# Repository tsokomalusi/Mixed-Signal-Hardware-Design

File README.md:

# Mixed-Signal-Hardware-Design

## 📌 Project Summary
This repository contains a mixed-signal hardware design project covering system-level design, schematic capture, analog simulation, and PCB layout.  
The project demonstrates best practices in analog/digital partitioning, component selection, simulation-driven design, and manufacturable PCB layout.

------------------------------------------------------------------------------------------------------------------------------------------------------------------------------------------
## 🧰 Tools Used
- **KiCad** – Schematic capture and PCB design  
- **LTSpice** – Analog circuit simulation  
- **STM32CubeIDE** – MCU pinout planning  
- **draw.io** – System block diagram
- **git and github** - version control system
-----------------------------------------------------------------------------------------------------------------------------------------------------------------------------------------
## 🧱 System Block Diagram

Refined version

-----------------------------------------------------------------------------------------------------------------------------------------------------------------------------------------
## 🧩 Pinout Planning

-----------------------------------------------------------------------------------------------------------------------------------------------------------------------------------------
## 📐 Schematic Design

Root Sheet

Power circuitry

MCU circuitry

ADC circuirty

DAC circuitry

Key design considerations:
- Proper decoupling and grounding
- Separation of analog and digital domains
- Power integrity and signal integrity

------------------------------------------------------------------------------------------------------------------------------------------------------------------------------------------
## 🧩 PCB Layout

### PCB STACKUP 
- TOP LAYER :     SIG/POWER
- IN1 LAYER:      GND
- IN2 LAYER:      GND
- BOTTOM LAYER:   SIG/POWER

###  PCB All Layers

### Top Layer

### Bottom Layer

### 3D View

PCB design highlights:
- Footprint creation
- Controlled impedance traces
- Avoiding: crosstalk, coupling, ground loops, inductance and radiation
- Via stitching, power puddles, keeping proper spacing between analog and digital circuits

-------------------------------------------------------------------------------------------------------------------------------------------------------------------------------------------
## 🔬 LTSpice Simulation

### AC Analysis Schematic

### AC Analysis Response

### DC Operating Point Analysis

------------------------------------------------------------------------------------------------------------------------------------------------------------------------------------------
## 📜 License
This project is released for educational and portfolio purposes.

------------------------------------------------------------------------------------------------------------------------------------------------------------------------------------------
## 🙏 Acknowledgements

This project was developed as part of hands-on learning inspired by the course:

**“Mixed-Signal Hardware Design with KiCad”**  
Instructor: **Philip Salmony**  
Platform: **FEDEVEL Academy**  
Website: https://www.fedevel.com

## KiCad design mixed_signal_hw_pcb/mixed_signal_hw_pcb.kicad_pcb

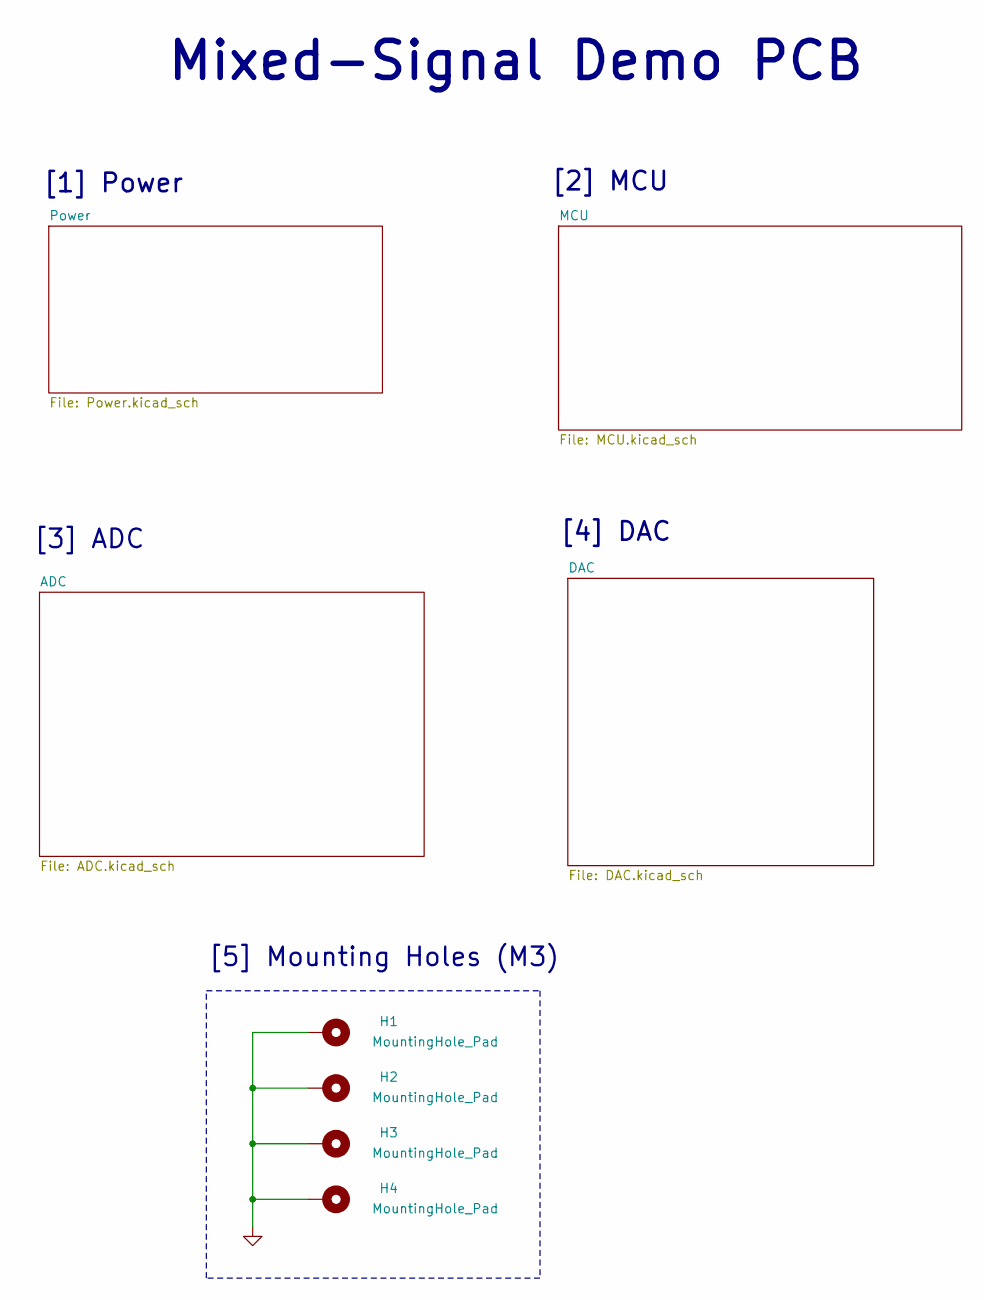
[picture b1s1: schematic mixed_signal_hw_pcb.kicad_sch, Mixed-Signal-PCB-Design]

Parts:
H1, H2, H3, H4: MountingHole_Pad; MountingHole_3.2mm_M3_Pad_Via

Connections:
GND: H1.1, H2.1, H3.1, H4.1; also elsewhere on the board

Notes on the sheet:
Mixed-Signal Demo PCB
[4] DAC
[5] Mounting Holes (M3)
[3] ADC
[2] MCU
[1] Power

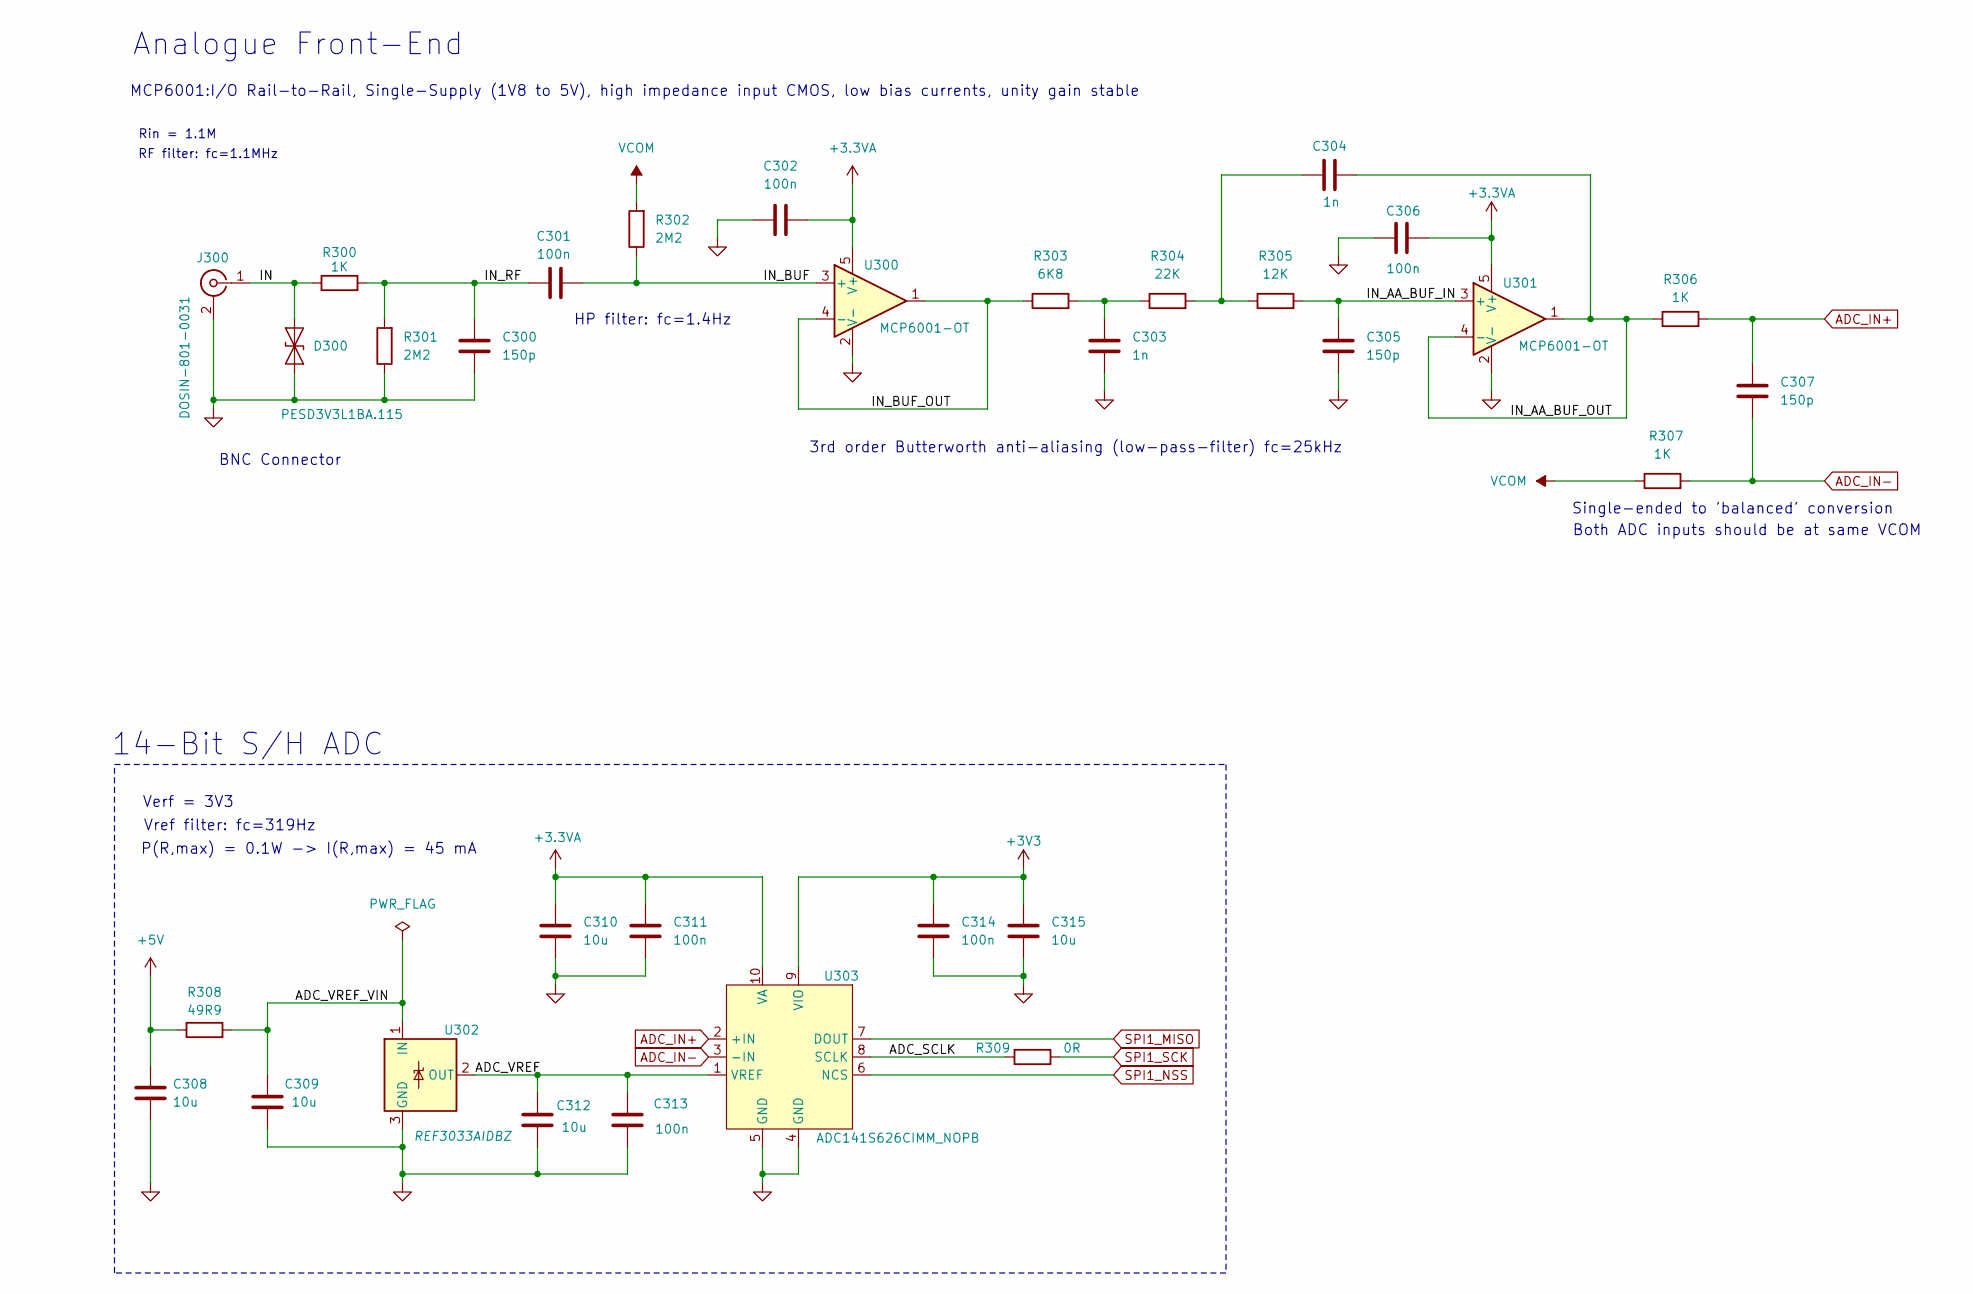
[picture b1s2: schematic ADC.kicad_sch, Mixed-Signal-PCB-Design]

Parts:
C300, C305, C307: 150p; C_0603_1608Metric; Manufacturer Part Number VJ0603A151JXAAC
C301, C302, C306, C311, C313, C314: 100n; C_0603_1608Metric; Manufacturer Part Number CC0603ZRY5V7BB104
C303, C304: 1n; C_0603_1608Metric; Manufacturer Part Number VJ0603H102KEBAO34
C308, C309, C310, C312, C315: 10u; C_0805_2012Metric; Manufacturer Part Number 0805X7R106KT1AT
D300: PESD3V3L1BA.115; D_SOD-323; Manufacturer Part Number PESD3V3L1BA,115
J300: DOSIN-801-0031; BNC; Manufacturer Part Number DOSIN-801-003
R300, R306, R307: 1K; R_0603_1608Metric; Manufacturer Part Number RC0603FR-071KL
R301, R302: 2M2; R_0805_2012Metric; Manufacturer Part Number RC0805FR-072M2L
R303: 6K8; R_0603_1608Metric; Manufacturer Part Number RC0603FR-076K8L
R304: 22K; R_0603_1608Metric; Manufacturer Part Number RC0603FR-0722KL
R305: 12K; R_0603_1608Metric; Manufacturer Part Number RC0603FR-0712KL
R308: 49R9; R_0603_1608Metric; Manufacturer Part Number RC0603FR-0749R9L
R309: 0R; R_0603_1608Metric; Manufacturer Part Number RC0603JR-070RL
U300, U301: MCP6001-OT; SOT-23-5; Manufacturer Part Number MCP6001-OT
U302: REF3033AIDBZ; SOT-23; Manufacturer Part Number REF3033AIDBZ
U303: ADC141S626CIMM_NOPB; SOIC-10; Manufacturer Part Number ADC141S626CIMM

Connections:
+3.3VA: C302.2, C306.2, C310.1, C311.1, U300.5 (V+), U301.5 (V+), U303.10 (VA); also elsewhere on the board
+3V3: C314.1, C315.1, U303.9 (VIO); also elsewhere on the board
+5V: C308.1, R308.1; also elsewhere on the board
/ADC/ADC_SCLK: R309.1, U303.8 (SCLK)
/ADC/ADC_VREF: C312.1, C313.1, U302.2 (OUT), U303.1 (VREF)
/ADC/ADC_VREF_VIN: C309.1, R308.2, U302.1 (IN)
/ADC/IN: D300.2 (A2), J300.1 (In), R300.1
/ADC/IN_AA_BUF_IN: C305.1, R305.2, U301.3 (+)
/ADC/IN_AA_BUF_OUT: C304.2, R306.1, U301.1, U301.4 (-)
/ADC/IN_BUF: C301.2, R302.1, U300.3 (+)
/ADC/IN_BUF_OUT: R303.1, U300.1, U300.4 (-)
/ADC/IN_RF: C300.1, C301.1, R300.2, R301.2
ADC_IN+: C307.1, R306.2, U303.2 (+IN)
ADC_IN-: C307.2, R307.2, U303.3 (-IN)
GND: C300.2, C302.1, C303.2, C305.2, C306.1, C308.2, C309.2, C310.2, C311.2, C312.2, C313.2, C314.2, C315.2, D300.1 (A1), J300.2 (Ext), R301.1, U300.2 (V-), U301.2 (V-), U302.3 (GND), U303.4 (GND), U303.5 (GND); also elsewhere on the board
unnamed: C303.1, R303.2, R304.1
unnamed: C304.1, R304.2, R305.1
SPI1_MISO: U303.7 (DOUT); also elsewhere on the board
SPI1_NSS: U303.6 (NCS); also elsewhere on the board
SPI1_SCK: R309.2; also elsewhere on the board
VCOM: R302.2, R307.1; also elsewhere on the board

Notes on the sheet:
Verf = 3V3
HP filter: fc=1.4Hz
BNC Connector
Rin = 1.1M
Vref filter: fc=319Hz
14-Bit S/H ADC
Single-ended to 'balanced' conversion
RF filter: fc=1.1MHz
P(R,max) = 0.1W -> I(R,max) = 45 mA
Analogue Front-End
3rd order Butterworth anti-aliasing (low-pass-filter) fc=25kHz
MCP6001:I/O Rail-to-Rail, Single-Supply (1V8 to 5V), high impedance input CMOS, low bias currents, unity gain stable
Both ADC inputs should be at same VCOM

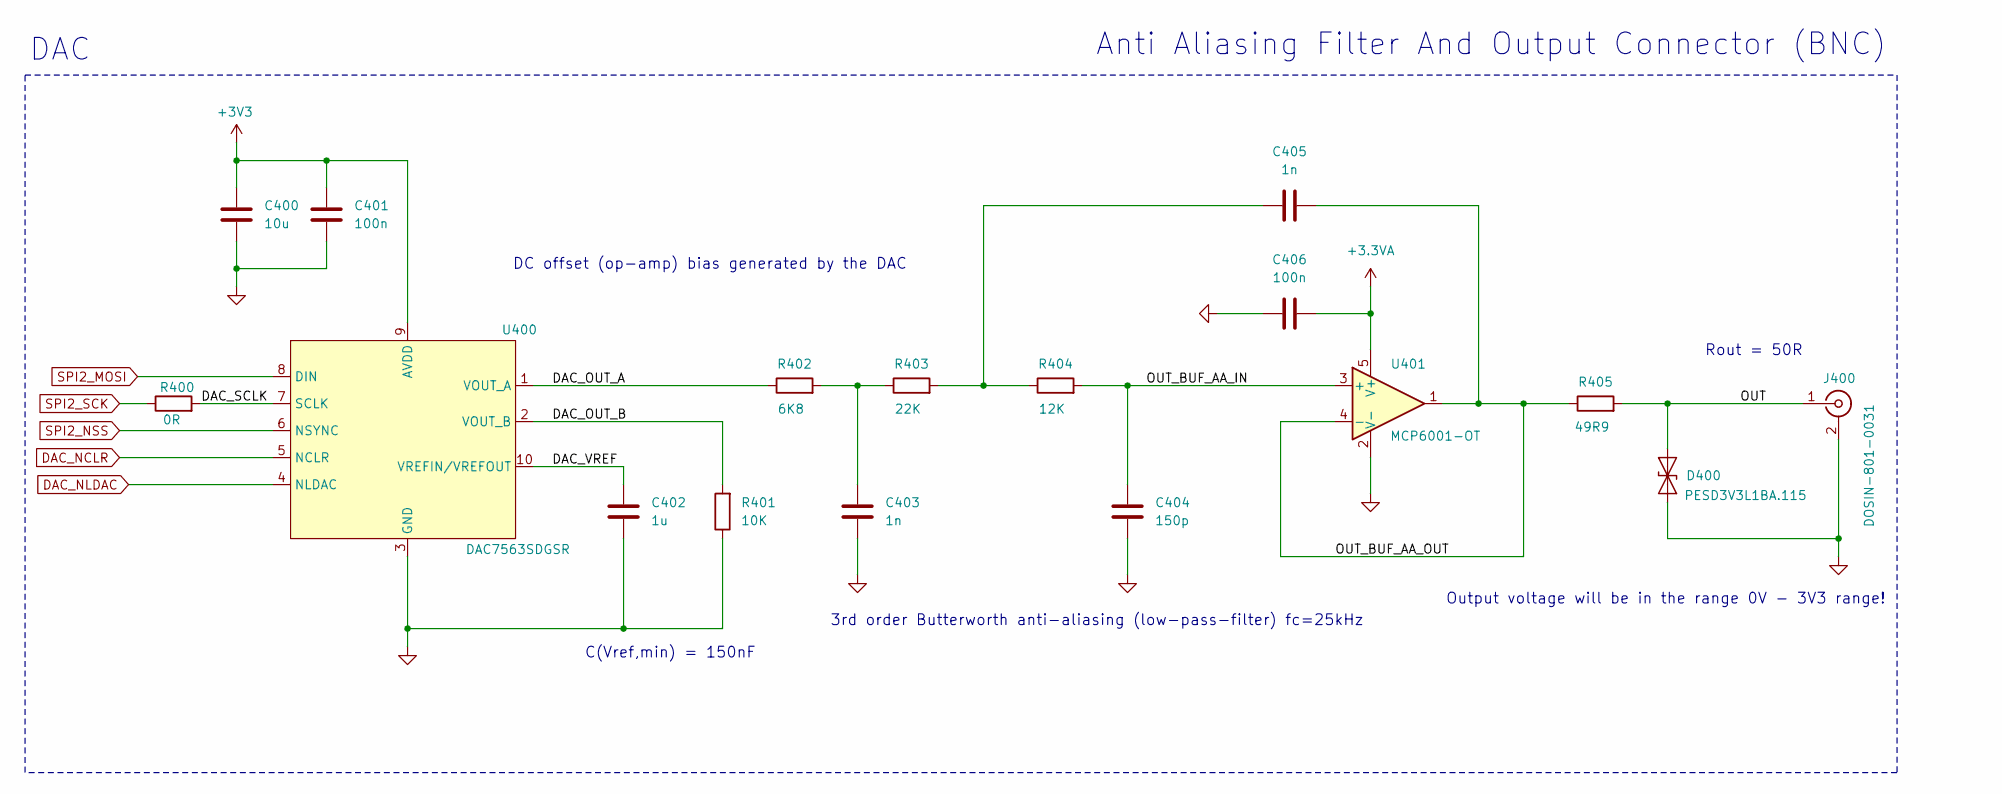
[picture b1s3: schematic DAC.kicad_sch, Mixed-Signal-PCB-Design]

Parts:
C400: 10u; C_0805_2012Metric; Manufacturer Part Number 0805X7R106KT1AT
C401, C406: 100n; C_0603_1608Metric; Manufacturer Part Number CC0603ZRY5V7BB104
C402: 1u; C_0805_2012Metric; Manufacturer Part Number 08055D105KAT2A
C403, C405: 1n; C_0603_1608Metric; Manufacturer Part Number VJ0603H102KEBAO34
C404: 150p; C_0603_1608Metric; Manufacturer Part Number VJ0603A151JXAAC
D400: PESD3V3L1BA.115; D_SOD-323; Manufacturer Part Number PESD3V3L1BA,115
J400: DOSIN-801-0031; BNC; Manufacturer Part Number DOSIN-801-003
R400: 0R; R_0603_1608Metric; Manufacturer Part Number RC0603JR-070RL
R401: 10K; R_0603_1608Metric; Manufacturer Part Number RC0603FR-0710KL
R402: 6K8; R_0603_1608Metric; Manufacturer Part Number RC0603FR-076K8L
R403: 22K; R_0603_1608Metric; Manufacturer Part Number RC0603FR-0722KL
R404: 12K; R_0603_1608Metric; Manufacturer Part Number RC0603FR-0712KL
R405: 49R9; R_0603_1608Metric; Manufacturer Part Number RC0603FR-0749R9L
U400: DAC7563SDGSR; SOIC-10; Manufacturer Part Number DAC7563SDGSR
U401: MCP6001-OT; SOT-23-5; Manufacturer Part Number MCP6001T‑I/OT

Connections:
+3.3VA: C406.2, U401.5 (V+); also elsewhere on the board
+3V3: C400.1, C401.1, U400.9 (AVDD); also elsewhere on the board
/DAC/DAC_OUT_A: R402.1, U400.1 (VOUT_A)
/DAC/DAC_OUT_B: R401.2, U400.2 (VOUT_B)
/DAC/DAC_SCLK: R400.2, U400.7 (SCLK)
/DAC/DAC_VREF: C402.1, U400.10 (VREFIN/VREFOUT)
/DAC/OUT: D400.2 (A2), J400.1 (In), R405.2
/DAC/OUT_BUF_AA_IN: C404.1, R404.2, U401.3 (+)
/DAC/OUT_BUF_AA_OUT: C405.2, R405.1, U401.1, U401.4 (-)
DAC_NCLR: U400.5 (NCLR); also elsewhere on the board
DAC_NLDAC: U400.4 (NLDAC); also elsewhere on the board
GND: C400.2, C401.2, C402.2, C403.2, C404.2, C406.1, D400.1 (A1), J400.2 (Ext), R401.1, U400.3 (GND), U401.2 (V-); also elsewhere on the board
unnamed: C403.1, R402.2, R403.1
unnamed: C405.1, R403.2, R404.1
SPI2_MOSI: U400.8 (DIN); also elsewhere on the board
SPI2_NSS: U400.6 (NSYNC); also elsewhere on the board
SPI2_SCK: R400.1; also elsewhere on the board

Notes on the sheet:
Output voltage will be in the range 0V - 3V3 range!
Anti Aliasing Filter And Output Connector (BNC)
C(Vref,min) = 150nF
3rd order Butterworth anti-aliasing (low-pass-filter) fc=25kHz
DAC
DC offset (op-amp) bias generated by the DAC
Rout = 50R

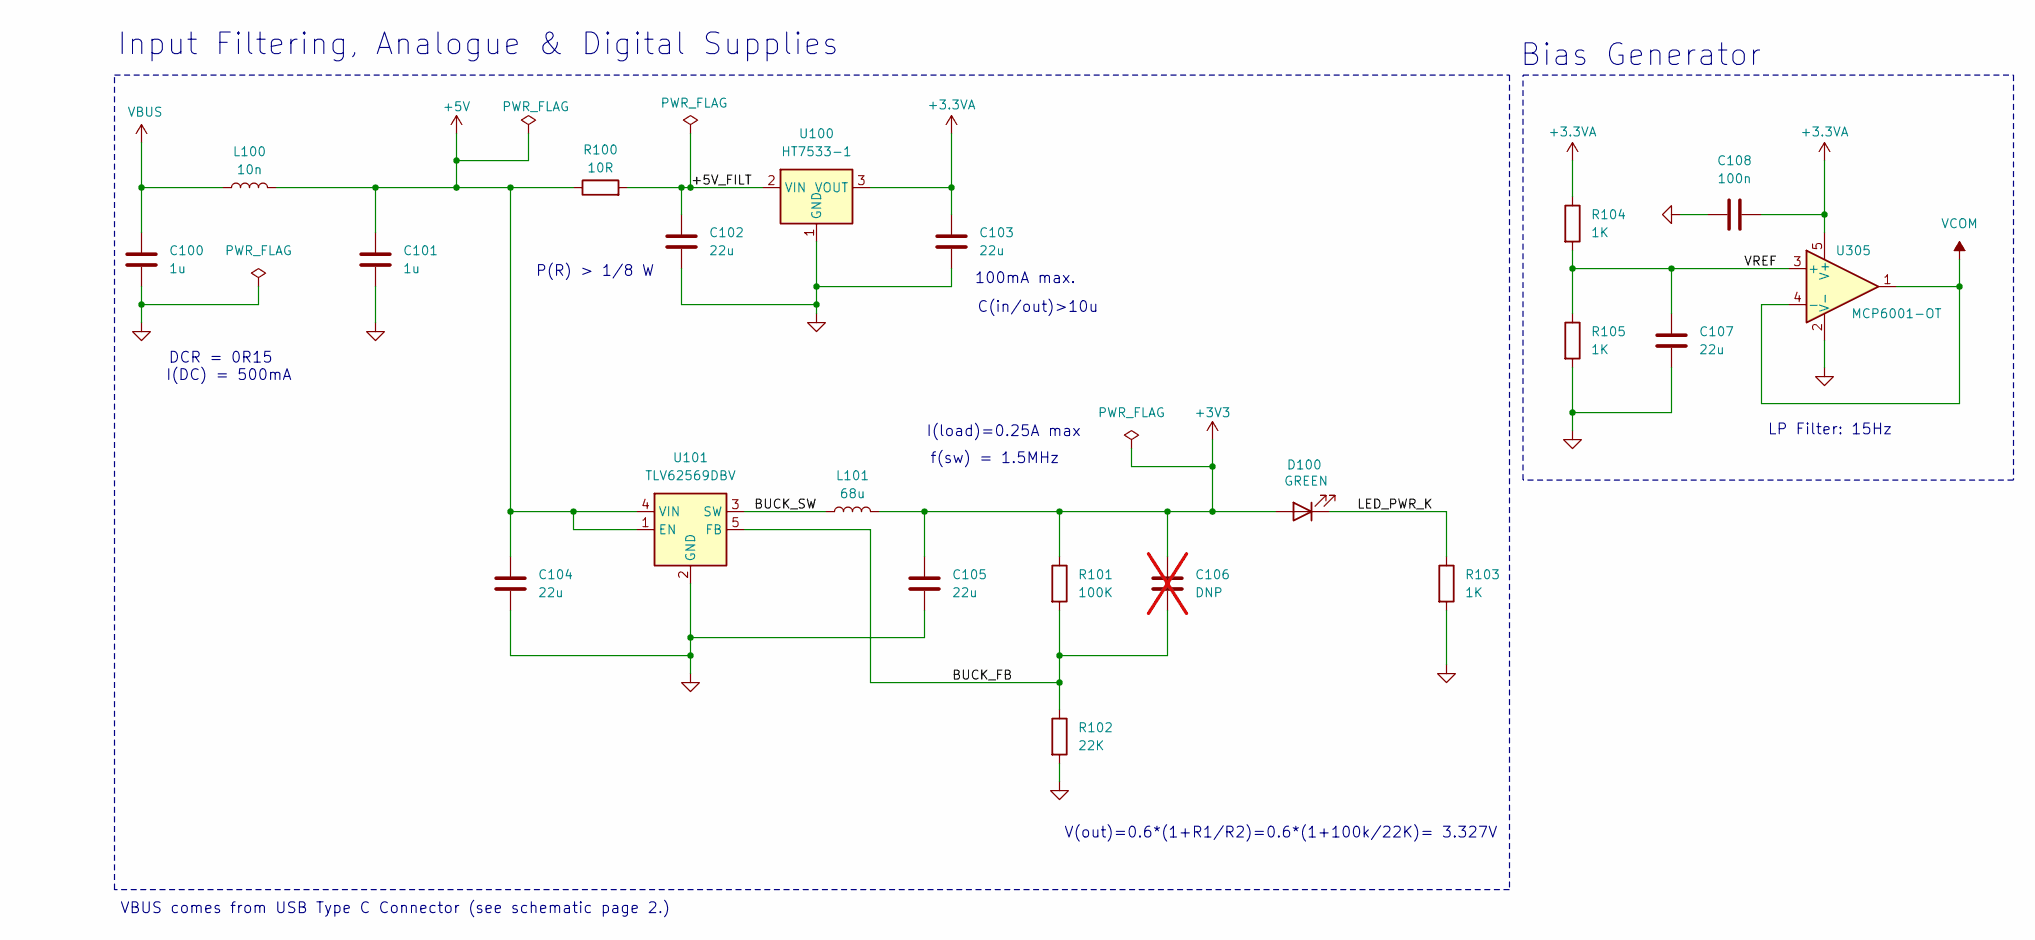
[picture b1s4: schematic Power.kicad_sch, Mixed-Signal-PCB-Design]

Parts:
C100, C101: 1u; C_0805_2012Metric; Manufacturer Part Number 08055D105KAT2A
C102, C103, C104, C105, C107: 22u; C_0805_2012Metric; Manufacturer Part Number 0805YD226MAT2A
C106: DNP; C_0805_2012Metric; not fitted
C108: 100n; C_0603_1608Metric; Manufacturer Part Number CC0603ZRY5V7BB104
D100: GREEN; D_0805_2012Metric; Manufacturer Part Number LTST-C170FKT
L100: 10n; L_0603_1608Metric; Manufacturer Part Number MWSA0603S-100J
L101: 68u; L_Sunlord_MWSA0603S; Manufacturer Part Number MWSA0603S-680K
R100: 10R; R_0603_1608Metric; Manufacturer Part Number RC0603FR-0710RL
R101: 100K; R_0603_1608Metric; Manufacturer Part Number RC0603FR-07100KL
R102: 22K; R_0603_1608Metric; Manufacturer Part Number RC0603FR-0722KL
R103, R104, R105: 1K; R_0603_1608Metric; Manufacturer Part Number RC0603FR-071KL
U100: HT7533-1; SOT-89-3; Manufacturer Part Number HT7533-1
U101: TLV62569DBV; SOT-23-5; Manufacturer Part Number TLV62569DBV
U305: MCP6001-OT; SOT-23-5; Manufacturer Part Number MCP6001-OT

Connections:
+3.3VA: C103.1, C108.2, R104.1, U100.3 (VOUT), U305.5 (V+); also elsewhere on the board
+3V3: C105.1, C106.1, D100.2 (A), L101.2, R101.1; also elsewhere on the board
+5V: C101.1, C104.1, L100.2, R100.1, U101.1 (EN), U101.4 (VIN); also elsewhere on the board
/Power/+5V_FILT: C102.1, R100.2, U100.2 (VIN)
/Power/BUCK_FB: C106.2, R101.2, R102.1, U101.5 (FB)
/Power/BUCK_SW: L101.1, U101.3 (SW)
/Power/LED_PWR_K: D100.1 (K), R103.1
/Power/VREF: C107.1, R104.2, R105.1, U305.3 (+)
GND: C100.2, C101.2, C102.2, C103.2, C104.2, C105.2, C107.2, C108.1, R102.2, R103.2, R105.2, U100.1 (GND), U101.2 (GND), U305.2 (V-); also elsewhere on the board
VBUS: C100.1, L100.1; also elsewhere on the board
VCOM: U305.1, U305.4 (-); also elsewhere on the board

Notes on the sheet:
DCR = 0R15 I(DC) = 500mA
V(out)=0.6*(1+R1/R2)=0.6*(1+100k/22K)= 3.327V
P(R) > 1/8 W
C(in/out)>10u
VBUS comes from USB Type C Connector (see schematic page 2.)
I(load)=0.25A max
100mA max.
Bias Generator
Input Filtering, Analogue & Digital Supplies
f(sw) = 1.5MHz
LP Filter: 15Hz

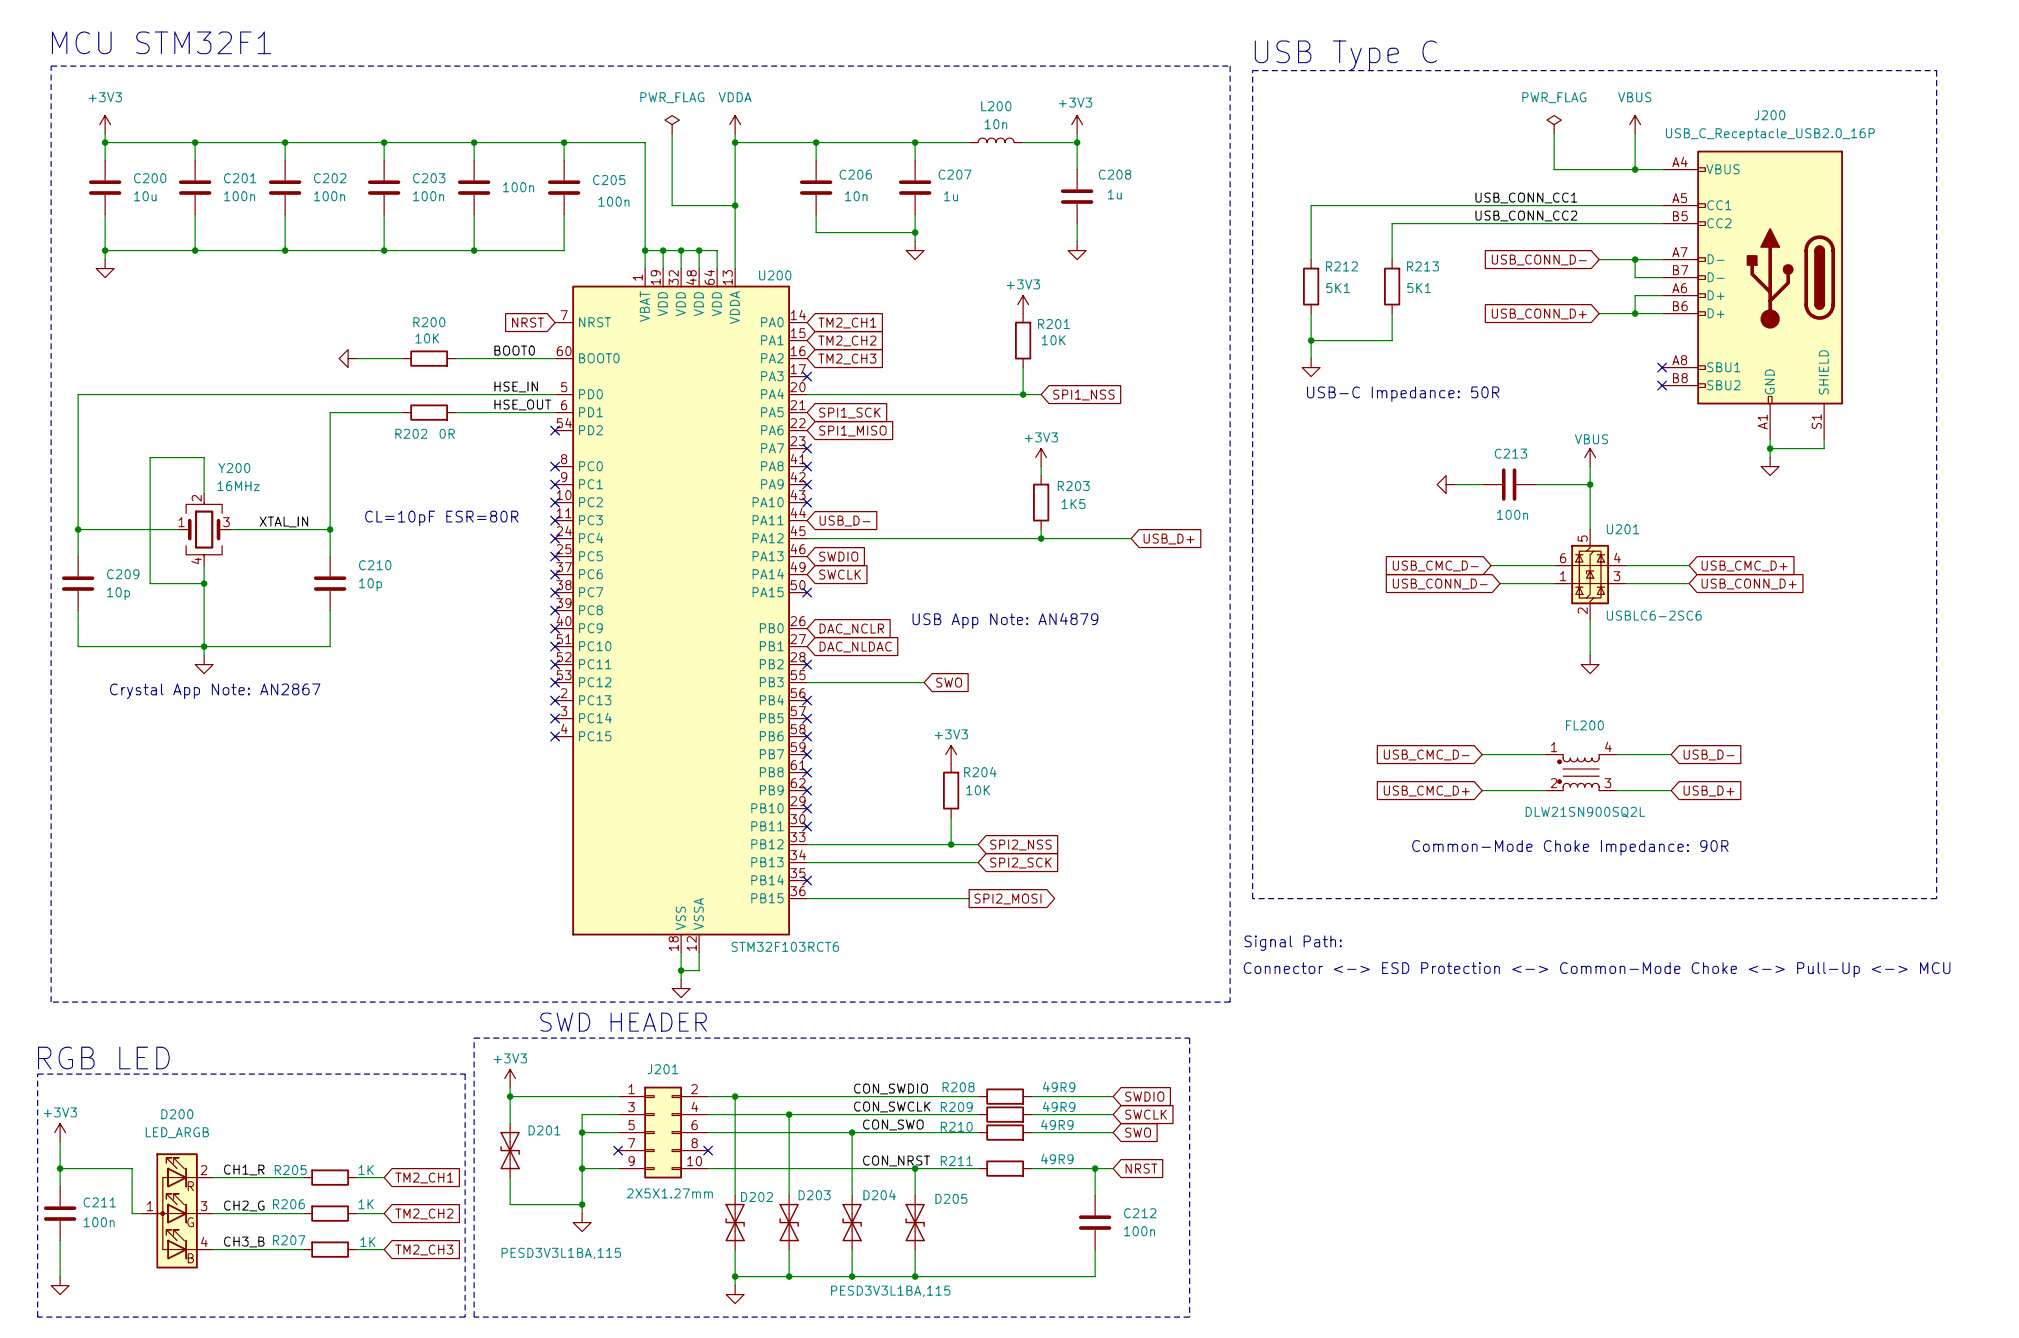
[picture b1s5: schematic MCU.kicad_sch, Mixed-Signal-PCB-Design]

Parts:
C200: 10u; C_0805_2012Metric; Manufacturer Part Number 0805X7R106KT1AT
C201, C202, C203, C204, C205, C211, C212, C213: 100n; C_0603_1608Metric; Manufacturer Part Number CC0603ZRY5V7BB104
C206: 10n; C_0603_1608Metric; Manufacturer Part Number VJ0603Y103KXJAC31X
C207, C208: 1u; C_0805_2012Metric; Manufacturer Part Number 08055D105KAT2A
C209, C210: 10p; C_0603_1608Metric; Manufacturer Part Number VJ0603A100FXBAC
D200: LED_ARGB; LED_AAA3528LSEEZGKQBKS_KNB; Manufacturer Part Number AAA3528LSEEZGKQBKS
D201, D202: PESD3V3L1BA,115; D_SOD-323; Manufacturer Part Number PESD3V3L1BA,115
D203, D204, D205: SD05_SOD323; D_SOD-323; Manufacturer Part Number PESD3V3L1BA,115
FL200: DLW21SN900SQ2L; choke; Manufacturer Part Number DLW21SN900SQ2L
J200: USB_C_Receptacle_USB2.0_16P; USB_C_Receptacle_HRO_TYPE-C-31-M-12; Manufacturer Part Number TYPE-C-31-M-12
J201: 2X5X1.27mm; PinHeader_2x05_P1.27mm_Vertical_SMD; Manufacturer Part Number FTSH-105-01-L-DV-K
L200: 10n; L_0603_1608Metric; Manufacturer Part Number LQW18AN10NJ00D
R200, R201, R204: 10K; R_0603_1608Metric; Manufacturer Part Number RC0603FR-0710KL
R202: 0R; R_0603_1608Metric; Manufacturer Part Number RC0603JR-070RL
R203: 1K5; R_0603_1608Metric; Manufacturer Part Number RC0603FR-071K5L
R205, R206, R207: 1K; R_0603_1608Metric; Manufacturer Part Number RC0603FR-071KL
R208, R209, R210, R211: 49R9; R_0603_1608Metric; Manufacturer Part Number RC0603FR-0749R9L
R212, R213: 5K1; R_0603_1608Metric; Manufacturer Part Number RC0603FR-075K1L
U200: STM32F103RCT6; LQFP-64_10x10mm_P0.5mm; Manufacturer Part Number STM32F103RCT6
U201: USBLC6-2SC6; SOT-23-6; Manufacturer Part Number USBLC6-2SC6
Y200: 16MHz; Crystal_SMD_3225-4Pin_3.2x2.5mm; Manufacturer Part Number FA-238 16.000 MHz

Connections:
+3V3: C200.1, C201.1, C202.1, C203.1, C204.1, C205.1, C208.1, C211.1, D200.1 (A), D201.2 (A2), J201.1, L200.2, R201.2, R203.2, R204.2, U200.1 (VBAT), U200.19 (VDD), U200.32 (VDD), U200.48 (VDD), U200.64 (VDD); also elsewhere on the board
/MCU/BOOT0: R200.2, U200.60 (BOOT0)
/MCU/CH1_R: D200.2 (RK), R205.2
/MCU/CH2_G: D200.3 (GK), R206.2
/MCU/CH3_B: D200.4 (BK), R207.2
/MCU/CON_NRST: D205.2 (A2), J201.10, R211.1
/MCU/CON_SWCLK: D203.2 (A2), J201.4, R209.1
/MCU/CON_SWDIO: D202.2 (A2), J201.2, R208.1
/MCU/CON_SWO: D204.2 (A2), J201.6, R210.1
/MCU/HSE_IN: C209.1, U200.5 (PD0), Y200.1
/MCU/HSE_OUT: R202.2, U200.6 (PD1)
/MCU/USB_CONN_CC1: J200.A5 (CC1), R212.2
/MCU/USB_CONN_CC2: J200.B5 (CC2), R213.2
/MCU/XTAL_IN: C210.1, R202.1, Y200.3
DAC_NCLR: U200.26 (PB0); also elsewhere on the board
DAC_NLDAC: U200.27 (PB1); also elsewhere on the board
GND: C200.2, C201.2, C202.2, C203.2, C204.2, C205.2, C206.2, C207.2, C208.2, C209.2, C210.2, C211.2, C212.2, C213.1, D201.1 (A1), D202.1 (A1), D203.1 (A1), D204.1 (A1), D205.1 (A1), J200.A1 (GND), J200.A12 (GND), J200.B1 (GND), J200.B12 (GND), J200.S1 (SHIELD), J201.3, J201.5, J201.9, R200.1, R212.1, R213.1, U200.12 (VSSA), U200.18 (VSS), U200.31 (VSS), U200.47 (VSS), U200.63 (VSS), U201.2 (GND), Y200.2, Y200.4; also elsewhere on the board
NRST: C212.1, R211.2, U200.7 (NRST)
SPI1_MISO: U200.22 (PA6); also elsewhere on the board
SPI1_NSS: R201.1, U200.20 (PA4); also elsewhere on the board
SPI1_SCK: U200.21 (PA5); also elsewhere on the board
SPI2_MOSI: U200.36 (PB15); also elsewhere on the board
SPI2_NSS: R204.1, U200.33 (PB12); also elsewhere on the board
SPI2_SCK: U200.34 (PB13); also elsewhere on the board
SWCLK: R209.2, U200.49 (PA14)
SWDIO: R208.2, U200.46 (PA13)
SWO: R210.2, U200.55 (PB3)
TM2_CH1: R205.1, U200.14 (PA0)
TM2_CH2: R206.1, U200.15 (PA1)
TM2_CH3: R207.1, U200.16 (PA2)
USB_CMC_D+: FL200.2, U201.4 (I/O1)
USB_CMC_D-: FL200.1, U201.6 (I/O1)
USB_CONN_D+: J200.A6 (D+), J200.B6 (D+), U201.3 (I/O2)
USB_CONN_D-: J200.A7 (D-), J200.B7 (D-), U201.1 (I/O2)
USB_D+: FL200.3, R203.1, U200.45 (PA12)
USB_D-: FL200.4, U200.44 (PA11)
VBUS: C213.2, J200.A4 (VBUS), J200.A9 (VBUS), J200.B4 (VBUS), J200.B9 (VBUS), U201.5 (VBUS); also elsewhere on the board
VDDA: C206.1, C207.1, L200.1, U200.13 (VDDA)

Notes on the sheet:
Crystal App Note: AN2867
CL=10pF ESR=80R
Connector <-> ESD Protection <-> Common-Mode Choke <-> Pull-Up <-> MCU
USB App Note: AN4879
RGB LED
Signal Path:
SWD HEADER
Common-Mode Choke Impedance: 90R
USB-C Impedance: 50R
USB Type C
MCU STM32F1

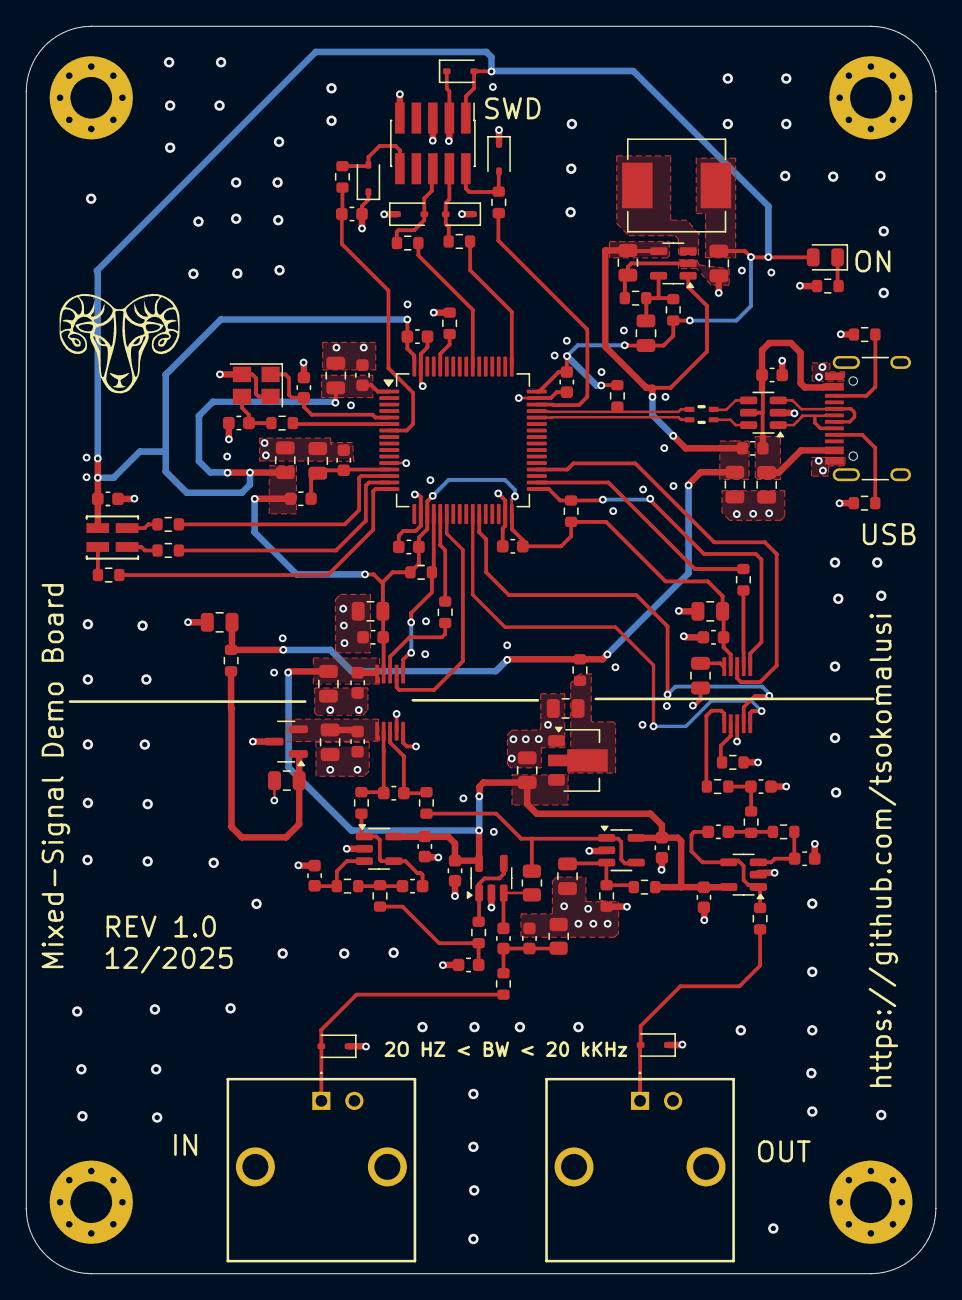
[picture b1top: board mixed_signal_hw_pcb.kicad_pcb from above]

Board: 4 copper layers, 70.0 x 96.0 mm, 115 parts (0 on the bottom side), 68 nets.

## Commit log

2025-12-28 uploading design files
2025-12-28 schematic files upload
